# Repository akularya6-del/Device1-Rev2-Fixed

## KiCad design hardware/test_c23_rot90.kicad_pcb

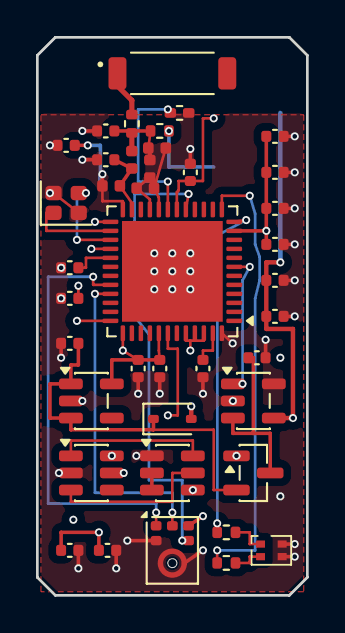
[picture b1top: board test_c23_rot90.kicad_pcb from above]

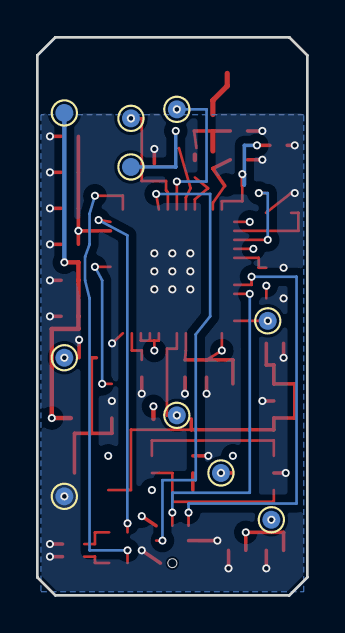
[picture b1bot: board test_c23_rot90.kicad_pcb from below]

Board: 4 copper layers, 15.0 x 31.0 mm, 50 parts (10 on the bottom side), 33 nets.

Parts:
ANT1: 0868AT43A0020E; Johanson_0868AT43A0020E_CUSTOM
C1, C2, C3, C4, C5, C7, C8, C9, C10, C11, C12, C13, C14, C15, C16, C17, C18, C20, C21: C_0402_1005Metric
C22, C23: 1.5pF; C_0402_1005Metric
D1: D_SOD-323
D2: LED_LiteOn_LTST-C295K_1.6x0.8mm
L1: L_0402_1005Metric
L2: 47nH; L_0402_1005Metric
L3: 18nH; L_0402_1005Metric
MK1: Knowles_SPH0645LM4H-6_3.5x2.65mm
Q1: SOT-23-6
Q2: SOT-23
R1, R6, R7: R_0402_1005Metric
R_ANT: R_0402_1005Metric
R_TEST: R_0402_1005Metric
TP_3V3: TestPoint_Pad_D1.0mm
TP_BATT_N: TestPoint_Pad_D1.0mm
TP_BATT_P: TestPoint_Pad_D1.0mm
TP_BOOT0: TestPoint_Pad_D1.0mm
TP_GND: TestPoint_Pad_D1.0mm
TP_NRST: TestPoint_Pad_D1.0mm
TP_RF: TestPoint_Pad_D1.0mm
TP_SWCLK: TestPoint_Pad_D1.0mm
TP_SWDIO: TestPoint_Pad_D1.0mm
TP_VBUS: TestPoint_Pad_D1.0mm
U1: QFN-48-1EP_7x7mm_P0.5mm_EP5.6x5.6mm
U2, U5: SOT-23-5
U4: SOT-23-6
Y1: Crystal_SMD_2016-4Pin_2.0x1.6mm

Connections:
/3V3: C1.1, C2.1, C3.1, C5.1, C8.1, C15.1, C16.1, C20.1, C21.1, MK1.5, TP_3V3.1, U1.11, U1.25, U1.28, U1.37, U1.41, U1.44, U1.45, U1.46, U5.5
/ANT_FEED: ANT1.1, R_ANT.2
/BATT_NEG: Q1.4, TP_BATT_N.1, U4.6
/BATT_POS: TP_BATT_P.1, U4.5
/BOOT0: R1.1, TP_BOOT0.1, U1.19
/CHG_STAT: U1.7, U2.1
/GATE_OC: Q1.5, U4.3
/GATE_OD: Q1.6, U4.1
/GND: C1.2, C2.2, C3.2, C4.2, C5.2, C7.2, C8.2, C9.2, C10.2, C11.2, C12.2, C13.2, C14.2, C15.2, C16.2, C17.2, C18.2, C20.2, C21.2, C23.1, D2.3, D2.4, MK1.2, MK1.3, Q1.1, R1.2, TP_GND.1, U1.48, U1.49, U2.2, U2.5, U4.2, U5.2, Y1.2, Y1.4
/LED_B: D2.2, R7.2
/LED_B_DRV: R7.1, U1.13
/LED_R: D2.1, R6.2
/LED_R_DRV: R6.1, U1.12
/MIC_SCK: MK1.4, U1.17
/MIC_SD: MK1.6, U1.33
/MIC_WS: MK1.1, U1.32
/NRST: C11.1, TP_NRST.1, U1.18
/OSC_IN: U1.26, Y1.1
/OSC_OUT: U1.27, Y1.3
/RFI_N: C23.2, L3.1, U1.21
/RFI_P: C22.2, L3.2, U1.20
/RFO_HP: C13.1, L1.1, L2.2, U1.23
/RF_50OHM: C14.1, C22.1, L1.2, R_ANT.1, R_TEST.1
/SWCLK: TP_SWCLK.1, U1.42
/SWDIO: TP_SWDIO.1, U1.36
/SYS_PWR: C9.1, D1.1, Q2.2, U5.1, U5.3
/TP_RF: R_TEST.2, TP_RF.1
/VBAT_PROT: C17.1, Q2.3, U2.3
/VBUS_5V: C10.1, C18.1, D1.2, Q2.1, TP_VBUS.1, U2.4
/VDDRF1V55: C7.1, U1.29
/VLXSMPS: C12.1, U1.47
/VR_PA: C4.1, L2.1, U1.24
unnamed: Q1.2, Q1.3
